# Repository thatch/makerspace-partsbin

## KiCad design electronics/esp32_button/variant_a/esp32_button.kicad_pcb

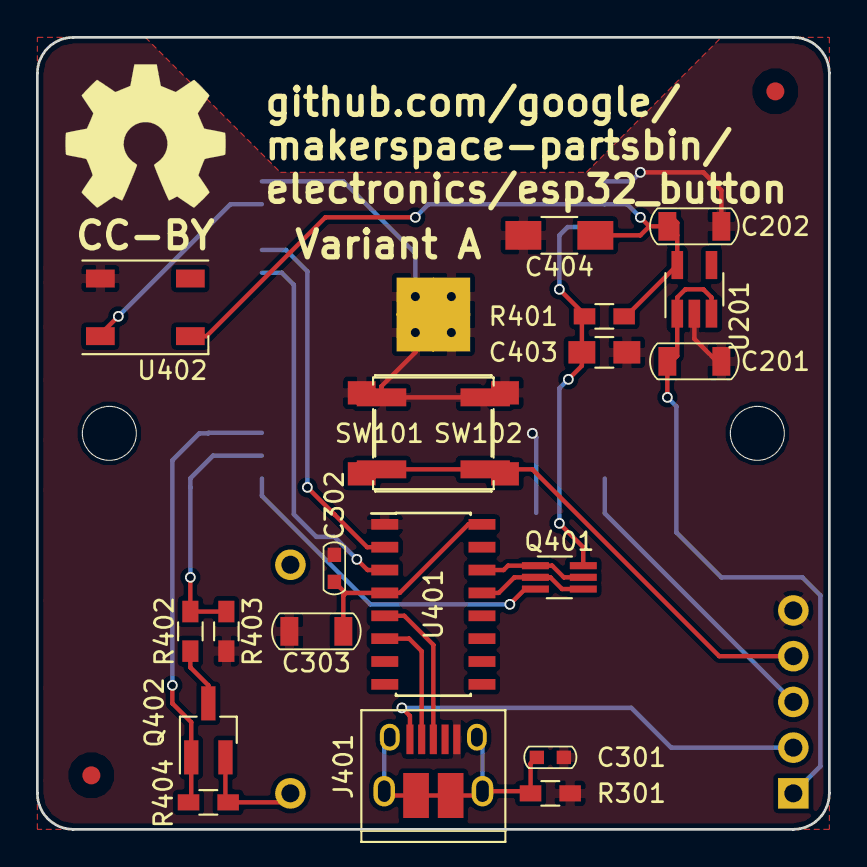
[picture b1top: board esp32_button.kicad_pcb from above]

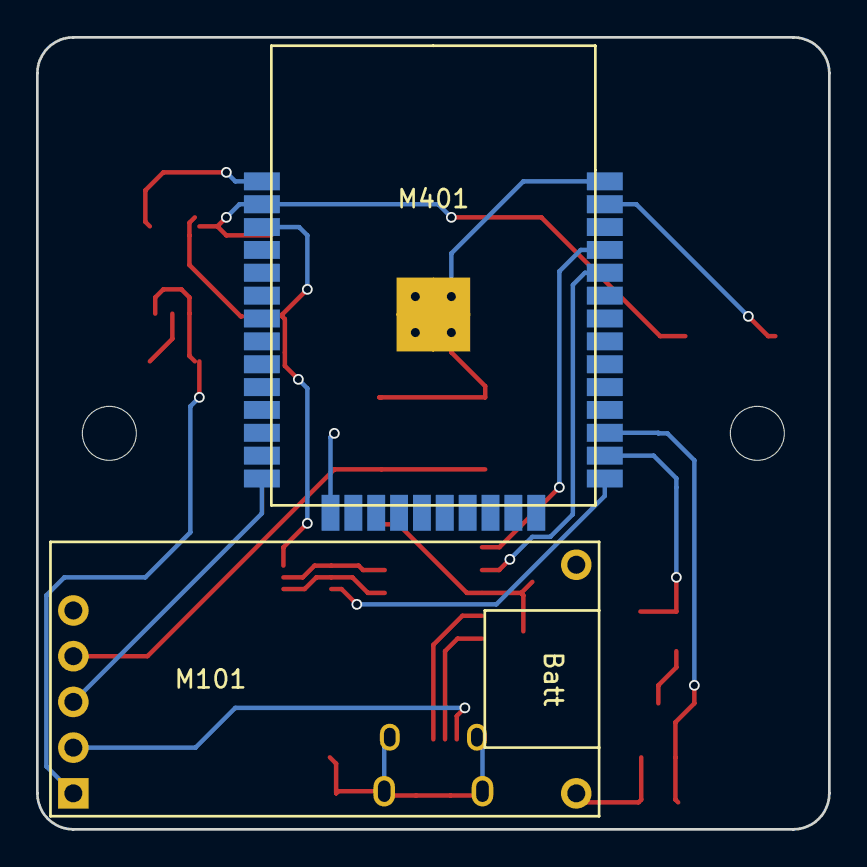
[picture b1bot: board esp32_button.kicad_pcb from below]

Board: 2 copper layers, 44.0 x 44.0 mm, 27 parts (2 on the bottom side), 21 nets.

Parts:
C201, C202, C303: 10u; C_1206
C301: 4.7n; C_0603
C302: 0.1u; C_0603
C403: 1u; C_0805_HandSoldering
C404: 47u; C_1206_HandSoldering
J401: USB_OTG; USB_Micro-B_10103594-0001LF
M101: STEPUP_SWITCH_V1
M401: WROOM32
P101, P102: FID; Fiducial_1mm_Dia_2.54mm_Outer_CopperTop
P103: OSHW; OSHW-Symbol_8.9x8mm_SilkScreen
P104, P105: HOLE; MountingHole_3mm
Q401: UMH3N; SOT-363_SC-70-6_Handsoldering
Q402: AO3401; SOT-23_Handsoldering
R301: 1M; R_0603_HandSoldering
R401, R402, R403, R404: 10k; R_0603_HandSoldering
SW101: SW_Push; SW_SPST_EVQP0
SW102: SW_Push; SW_SPST_PTS645
U201: ME6211; SOT-23-5_HandSoldering
U401: CH340C; SOIC-16_3.9x9.9mm_Pitch1.27mm
U402: 5050_Serial_RGB; LED_WS2812B-PLCC4

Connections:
/esp_module/BATTV: M101.7, Q402.2, R404.1
/esp_module/CHIP_PD: C403.1, M401.3, Q401.6, R401.2
/esp_module/IO0: M401.25, Q401.3
/esp_module/KEEPALIVE: M101.3, M401.14
/esp_module/RXD: M401.34, U401.3
/esp_module/TXD: M401.35, U401.2
/power/3V3OUT: C202.1, C404.1, M401.2, R401.1, U201.5, U402.3
/power/5VIN: C201.1, M101.1, U201.1, U201.3
/usb/REGULATED_3V3: C302.1, C303.1, U401.4, U401.16
/usb/USB5V: J401.1, M101.2
/usb/~DTR: Q401.2, Q401.4, U401.13
/usb/~RTS: Q401.1, Q401.5, U401.14
GND: C201.2, C202.2, C301.2, C302.2, C303.2, C403.2, C404.2, J401.5, M101.5, M401.1, M401.15, M401.38, M401.39, R301.2, R403.2, SW101.2, SW102.2, U201.2, U401.1, U402.1
unnamed: C301.1, J401.6, R301.1
unnamed: J401.2, U401.6
unnamed: J401.3, U401.5
unnamed: M101.4, SW101.1, SW102.1
unnamed: M401.26, R402.2, R403.1
unnamed: M401.27, Q402.1, R404.2
unnamed: M401.37, U402.2
unnamed: Q402.3, R402.1

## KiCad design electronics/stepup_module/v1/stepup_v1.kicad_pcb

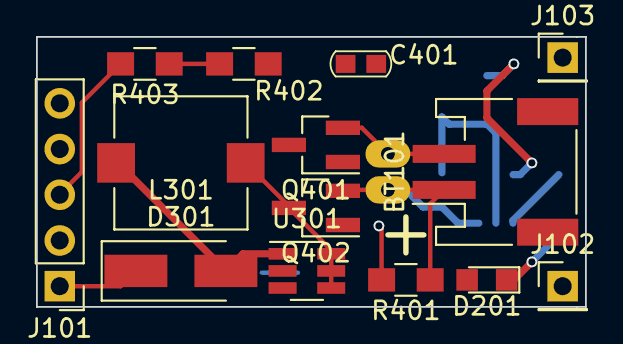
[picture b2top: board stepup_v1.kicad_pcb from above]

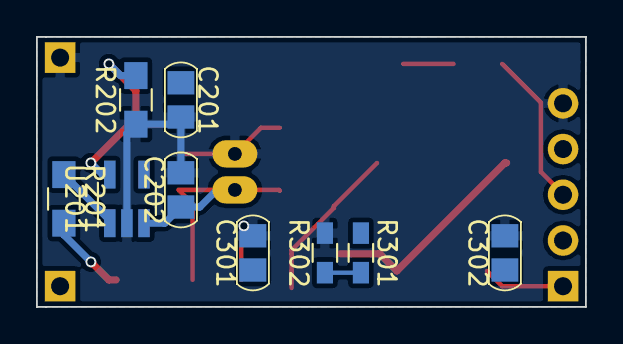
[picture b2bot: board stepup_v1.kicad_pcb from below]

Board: 2 copper layers, 30.5 x 15.0 mm, 23 parts (9 on the bottom side), 13 nets.

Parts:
BT101: Battery_Cell; JST_PH_2_Combo
C201, C202: 4.7u; C_0805
C301, C302: 22u; C_0805
C401: 220p; C_0603
D201: CHARGE; LED_0805
D301: D_Schottky; D_SMA_Handsoldering
J101: CONN_01X05; Pin_Header_Straight_1x05_Pitch2.54mm
J102: BATT+; Pin_Header_Straight_1x01_Pitch2.54mm
J103: BATT-; Pin_Header_Straight_1x01_Pitch2.54mm
L301: L; L_7.3x7.3_Handsoldering
Q401: AO3400; SOT-23_Handsoldering
Q402: AO3401; SOT-23_Handsoldering
R201: 1k; R_0805_HandSoldering
R202: R; R_0805_HandSoldering
R301, R302: R; R_0603_HandSoldering
R401, R402: 100k; R_0805_HandSoldering
R403: 10k; R_0805_HandSoldering
U201: MCP73831; SOT-23-5_HandSoldering
U301: SX1308; SOT-23-6_Handsoldering

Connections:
/booster/BATT: C301.1, J102.1, L301.1, Q402.3, U301.4, U301.5, U301.6
/booster/OUT: C302.1, D301.1, J101.1, R301.1
/booster/Vsw: D301.2, L301.2, U301.1
/charger/5V_IN: C201.1, D201.2, J101.2, U201.4
/charger/BATT: BT101.1, C202.1, Q402.2, R401.1, U201.3
/cut_power/KEEPALIVE: J101.3, R403.2
/cut_power/~POWERON: C401.1, J101.4, Q401.3, Q402.1, R401.2
GND: BT101.2, C201.2, C202.2, C301.2, C302.2, C401.2, J101.5, J103.1, Q401.2, R202.1, R302.2, R402.2, U201.2, U301.2
unnamed: D201.1, R201.2
unnamed: Q401.1, R402.1, R403.1
unnamed: R201.1, U201.1
unnamed: R202.2, U201.5
unnamed: R301.2, R302.1, U301.3

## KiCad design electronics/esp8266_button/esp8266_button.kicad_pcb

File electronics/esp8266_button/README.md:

Intended to be the same size as a 1200mah lipo.

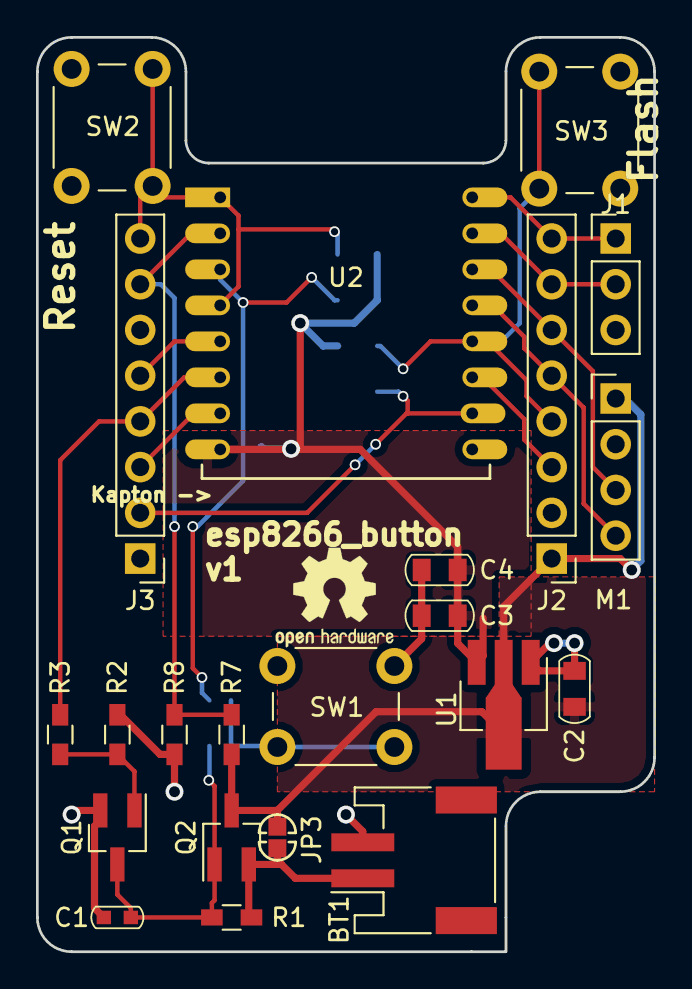
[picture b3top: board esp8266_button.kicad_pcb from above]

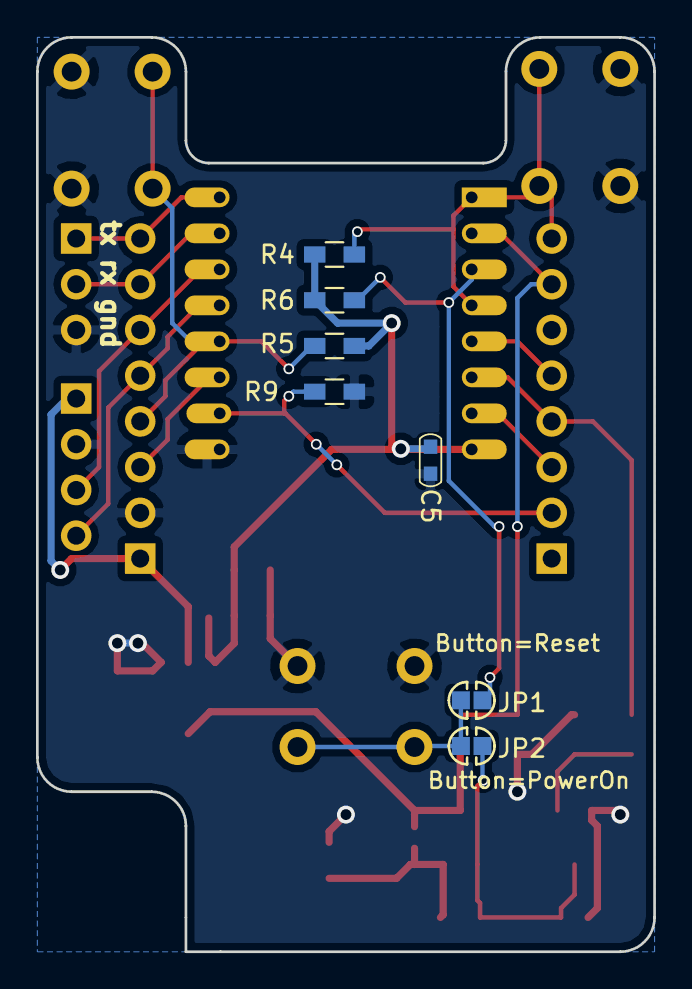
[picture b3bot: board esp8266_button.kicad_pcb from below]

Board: 2 copper layers, 34.3 x 50.8 mm, 30 parts (7 on the bottom side), 20 nets.

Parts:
BT1: Battery_Cell; JST_PH_S2B-PH-SM4-TB_02x2.00mm_Angled
C1: 220p; C_0603
C2, C3, C4: 10u; C_0805
C5: 0.1u; C_0603
J1: CONN_01X03; Pin_Header_Straight_1x03_Pitch2.54mm
J2, J3: CONN_01X08; Pin_Header_Straight_1x08_Pitch2.54mm
JP1: Button=Reset; SJ_1_NO
JP2: Button=PowerOn; SJ_1_NO
JP3: Always On; SJ_1_NO
M1: BMP180_Breakout; Pin_Header_Straight_1x04_Pitch2.54mm
P1: SYMBOL; OSHW-Logo2_7.3x6mm_SilkScreen
Q1: Q_NMOS_GSD; SOT-23_Handsoldering
Q2: Q_PMOS_GSD; SOT-23_Handsoldering
R1: 100k; R_0603_HandSoldering
R2: 220k; R_0603_HandSoldering
R3, R4, R5, R6, R9: 10k; R_0603_HandSoldering
R7, R8: R; R_0603_HandSoldering
SW1, SW2, SW3: SW_Push; SW_PUSH_6mm
U1: MCP1703A-3302/MB; SOT-89-3_Handsoldering
U2: ESP-12

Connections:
+3V3: C3.1, C4.1, C5.1, R4.1, R5.1, R6.1, U1.3, U2.8
/ADC: J3.7, R7.2, R8.1, U2.2
/GPIO2: J2.3, U2.11
/GPIO4: J2.5, M1.4, U2.13
/GPIO5: J2.6, M1.3, U2.14
/GPIO13: J3.3, U2.7
/GPIO14: J3.5, U2.5
/GPIO15: J3.2, R9.1, U2.10
/RXD: J1.2, J2.7, U2.15
/TXD: J1.1, J2.8, U2.16
/Vbat: BT1.1, JP3.1, Q2.2, R1.1
BATTMON: C2.1, J2.1, JP3.2, M1.1, Q2.3, R7.1, U1.2
CH_PD: JP1.2, R6.2, U2.3
GND: BT1.2, C1.2, C2.2, C3.2, C4.2, C5.2, J1.3, J2.2, M1.2, Q1.2, R2.2, R8.2, R9.2, SW1.1, SW2.1, SW3.1, U1.1, U2.9
GPIO0: J2.4, R5.2, SW3.2, U2.12
GPIO12: J3.4, R3.1, U2.6
unnamed: JP1.1, JP2.1, SW1.2
unnamed: Q1.1, R2.1, R3.2
RESET: J3.8, R4.2, SW2.2, U2.1, U2.4
~POWERON: C1.1, JP2.2, Q1.3, Q2.1, R1.2

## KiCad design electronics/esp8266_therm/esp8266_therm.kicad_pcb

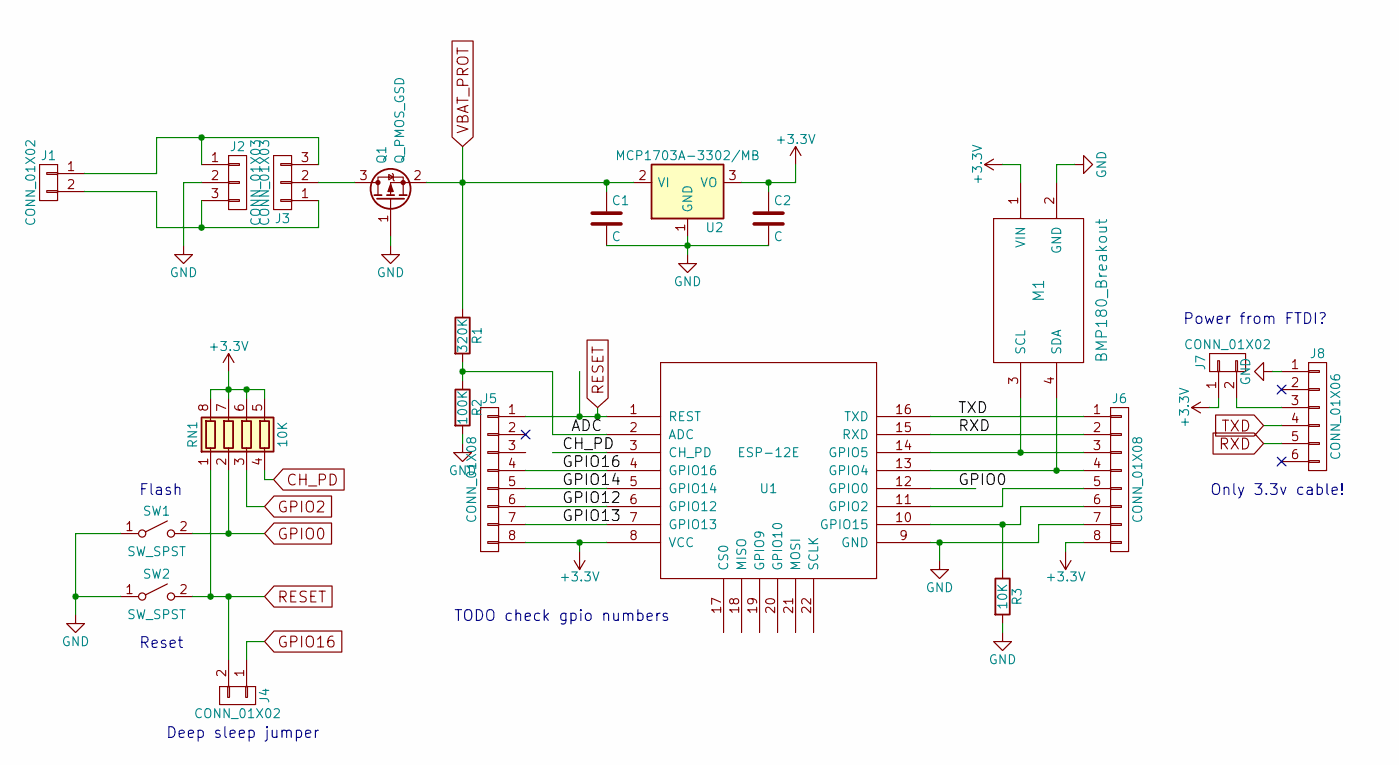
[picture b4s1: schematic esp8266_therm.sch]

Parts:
C1, C2: C; C_0805_HandSoldering
J1: CONN_01X02; JST_PH_S2B-PH-K_02x2.00mm_Angled
J2, J3: CONN_01X03; Pin_Header_Straight_1x03_Pitch2.54mm
J4, J7: CONN_01X02; Pin_Header_Straight_1x02_Pitch2.54mm
J5, J6: CONN_01X08; Pin_Header_Straight_1x08_Pitch2.54mm
J8: CONN_01X06; Pin_Header_Angled_1x06_Pitch2.54mm
M1: BMP180_Breakout; Pin_Header_Straight_1x04_Pitch2.54mm
Q1: Q_PMOS_GSD; SOT-23_Handsoldering
R1: 320K; R_0603_HandSoldering
R2: 100K; R_0603_HandSoldering
R3: 10K; R_0603_HandSoldering
RN1: 10K; R_Array_Concave_4x0603
SW1, SW2: SW_SPST; TACT_4x3
U1: ESP-12E; ESP-12E_SMD
U2: MCP1703A-3302/MB; SOT89-3_Housing

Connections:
+3V3: C2.1, J5.8, J6.8, J7.1, M1.1 (VIN), RN1.5 (R4.2), RN1.6 (R3.2), RN1.7 (R2.2), RN1.8 (R1.2), U1.8 (VCC), U2.3 (VO)
/ADC: R1.2, R2.1, U1.2 (ADC)
/GPIO12: J5.6, U1.6 (GPIO12)
/GPIO13: J5.7, U1.7 (GPIO13)
/GPIO14: J5.5, U1.5 (GPIO14)
CH_PD: RN1.4 (R4.1), U1.3 (CH_PD)
GND: C1.2, C2.2, J2.2, J6.7, J8.1, M1.2 (GND), Q1.1 (G), R2.2, R3.2, SW1.1 (A), SW2.1 (A), U1.9 (GND), U2.1 (GND)
GPIO0: RN1.2 (R2.1), SW1.2 (B), U1.12 (GPIO0)
GPIO16: J4.1, J5.4, U1.4 (GPIO16)
unnamed: J1.1, J2.1, J3.3
unnamed: J1.2, J2.3, J3.1
unnamed: J3.2, Q1.3 (D)
unnamed: J6.3, M1.3 (SCL), U1.14 (GPIO5)
unnamed: J6.4, M1.4 (SDA), U1.13 (GPIO4)
unnamed: J6.5, U1.11 (GPIO2)
unnamed: J6.6, R3.1, U1.10 (GPIO15)
unnamed: J7.2, J8.3
RESET: J4.2, J5.1, RN1.1 (R1.1), SW2.2 (B), U1.1 (REST)
RXD: J6.2, J8.5, U1.15 (RXD)
TXD: J6.1, J8.4, U1.16 (TXD)
VBAT_PROT: C1.1, Q1.2 (S), R1.1, U2.2 (VI)

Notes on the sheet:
Deep sleep jumper
Flash
Reset
Only 3.3v cable!
Power from FTDI?
TODO check gpio numbers

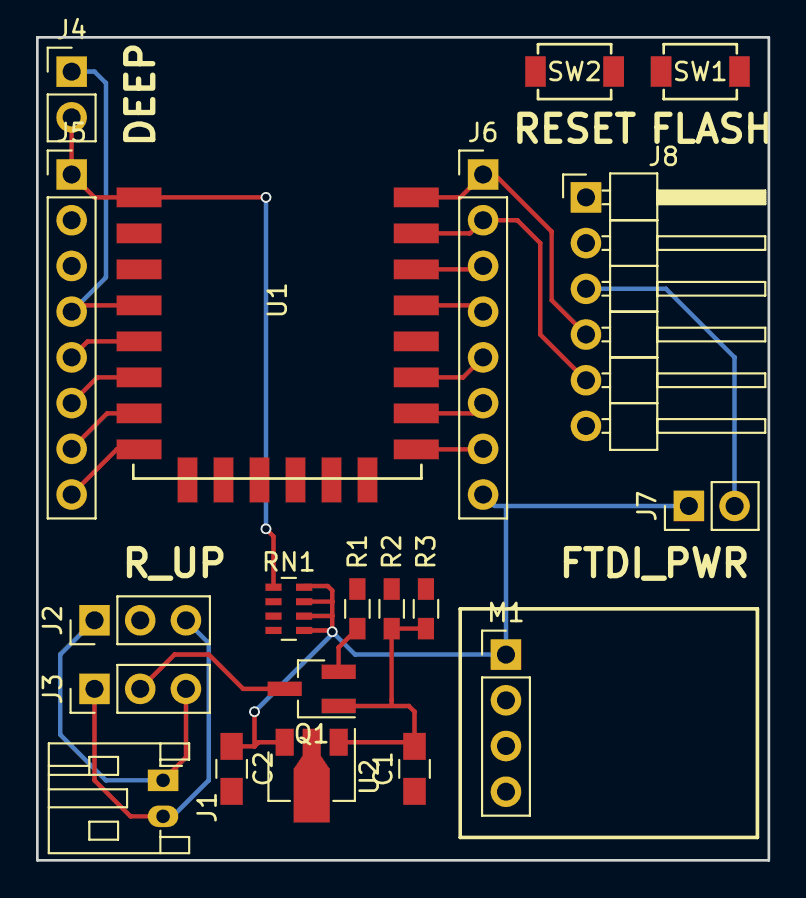
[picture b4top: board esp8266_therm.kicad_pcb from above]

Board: 2 copper layers, 40.6 x 45.7 mm, 20 parts (0 on the bottom side), 21 nets.

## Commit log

2017-07-14 Add some untested devboards I've been kicking around
2017-07-14 Beginning of wifi temp sensor
2017-07-14 Update pinout on board to match D1 mini
2017-07-14 Add smallish esp8288-based button
2017-07-16 Remove ground pour
2017-07-16 Checkpoint before bmp
2017-07-17 Fixup with bmp180
2017-07-17 sync
2017-08-17 Plated slots test
2017-10-18 Starting work on stepup module, with new footprints
2017-10-19 Lots of new libraries and esp32 board that uses stepup module
2017-10-19 Switch to -A and -B versions of esp32 button
2017-10-19 Untested micro usb mid-mount
2017-10-19 Add relative path fixer
2017-10-19 Relative path fixer force option to fix line endings
2017-10-19 Add convenience script for running the path fixer
    Eventually this can run the board renderer as well, and the footprint
    testing status exporter.
2017-10-19 Add generator for more readable BOMs
2017-10-19 Add license text and TODOs to schematic sheets
2017-10-19 Add generated BOM
2017-10-20 Add beginnings of svg renderer
2017-11-08 Bulk update starting on v0.2

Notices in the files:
electronics/esp32_button/variant_a/esp32_button.kicad_pcb:
CC-BY
